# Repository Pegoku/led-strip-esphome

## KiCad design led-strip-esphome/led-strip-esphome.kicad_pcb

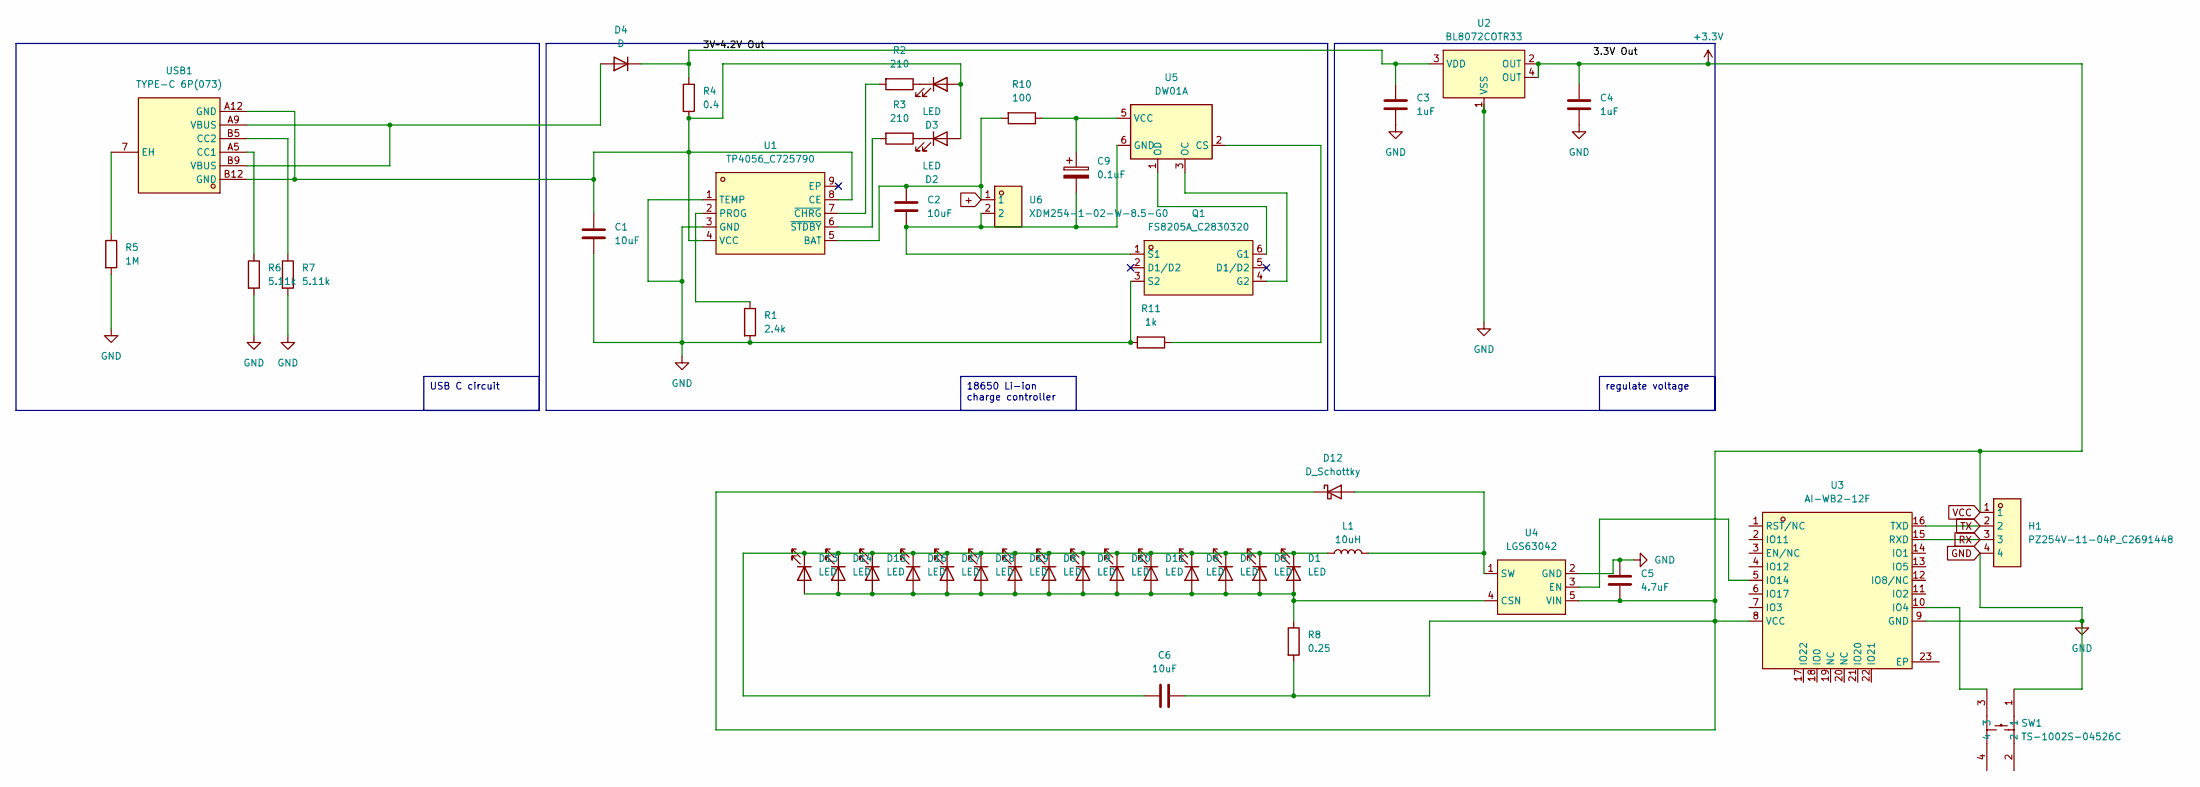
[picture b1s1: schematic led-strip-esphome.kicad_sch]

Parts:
C1, C2, C6: 10uF; C_0805_2012Metric
C3, C4: 1uF; C_0805_2012Metric
C5: 4.7uF; C_0805_2012Metric
C9: 0.1uF; CP_Elec_4x5.4
D1, D5, D6, D7, D8, D9, D10, D11, D13, D14, D15, D16, D17, D18, D19: LED; LED_PLCC_2835; LCSC C7423443
D2: LED; LED_0603_1608Metric; LCSC C22371297
D3: LED; LED_0603_1608Metric; LCSC C84263
D4: D; D_SMA; LCSC C5154212
D12: D_Schottky; D_SMA; LCSC C5350986
H1: PZ254V-11-04P_C2691448; HDR-TH_4P-P2.54-V-M; LCSC Part C2691448
L1: 10uH; L_Ferrocore_DLG-0403; LCSC C2929419
Q1: FS8205A_C2830320; SOT-23-6_L2.9-W1.6-P0.95-LS2.8-BR; LCSC Part C2830320
R1: 2.4k; LED_0805_2012Metric
R2, R3: 210; LED_0805_2012Metric
R4: 0.4; LED_0805_2012Metric
R5: 1M; LED_0805_2012Metric
R6, R7: 5.11k; LED_0805_2012Metric
R8: 0.25; LED_0805_2012Metric
R10: 100; LED_0805_2012Metric
R11: 1k; LED_0805_2012Metric
SW1: TS-1002S-04526C; SW-SMD_4P-L6.0-W6.0-P4.50-LS9.0-2; LCSC Part C455109
U1: TP4056_C725790; ESOP-8_L4.9-W3.9-P1.27-LS6.0-BL-EP; LCSC Part C725790
U2: BL8072COTR33; TO-252-3_L6.6-W6.1-P2.28-LS10.1-BL; LCSC Part C5155191
U3: AI-WB2-12F; COMM-SMD_22P-L24.0-W16.0-P2.00_ZIGBEE; LCSC Part C5187541
U4: LGS63042; SOT-23-5_L2.9-W1.6-P0.95-LS2.8-BL; LCSC Part C5123978
U5: DW01A; SOT-23-6
U6: XDM254-1-02-W-8.5-G0; HDR-TH_2P-P2.54-H-F-W10.0-N; LCSC Part C19268733
USB1: TYPE-C 6P(073); TYPE-C-SMD_TYPE-C-6P_5; LCSC Part C668623

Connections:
+: C2.2, R10.2, U1.5 (BAT), U6.1
/3V~4.2V Out: C3.1, D4.1 (K), R4.1, U2.3 (VDD)
GND: C1.1, C3.2, C4.2, C5.1, H1.4, Q1.3 (S2), R1.2, R5.2, R6.2, R7.2, R11.2, SW1.1, U1.1 (TEMP), U1.3 (GND), U2.1 (VSS), U3.9 (GND), U4.2 (GND)
unnamed: D1.2 (A), D5.2 (A), D6.2 (A), D7.2 (A), D8.2 (A), D9.2 (A), D10.2 (A), D11.2 (A), D13.2 (A), D14.2 (A), D15.2 (A), D16.2 (A), D17.2 (A), D18.2 (A), D19.2 (A), R8.1, U4.4 (CSN)
unnamed: C6.1, D1.1 (K), D5.1 (K), D6.1 (K), D7.1 (K), D8.1 (K), D9.1 (K), D10.1 (K), D11.1 (K), D13.1 (K), D14.1 (K), D15.1 (K), D16.1 (K), D17.1 (K), D18.1 (K), D19.1 (K), L1.1
unnamed: C1.2, D2.2 (A), D3.2 (A), R4.2, U1.4 (VCC), U1.8 (CE), USB1.A12 (GND), USB1.B12 (GND)
unnamed: D2.1 (K), R3.1
unnamed: D3.1 (K), R2.1
unnamed: D4.2 (A), USB1.A9 (VBUS), USB1.B9 (VBUS)
unnamed: D12.2 (A), L1.2, U4.1 (SW)
unnamed: Q1.6 (G1), U5.1 (OD)
unnamed: Q1.4 (G2), U5.3 (OC)
unnamed: C2.1, C9.2, Q1.1 (S1), U5.6 (GND), U6.2
unnamed: R1.1, U1.2 (PROG)
unnamed: R2.2, U1.7 (~CHRG)
unnamed: R3.2, U1.6 (~STDBY)
unnamed: SW1.3, U3.10 (IO4)
unnamed: U3.5 (IO14), U4.3 (EN)
unnamed: R11.1, U5.2 (CS)
unnamed: C9.1, R10.1, U5.5 (VCC)
unnamed: R6.1, USB1.A5 (CC1)
unnamed: R7.1, USB1.B5 (CC2)
unnamed: R5.1, USB1.7 (EH)
RX: H1.3, U3.15 (RXD)
TX: H1.2, U3.16 (TXD)
VCC: C4.1, C5.2, C6.2, D12.1 (K), H1.1, R8.2, U2.2 (OUT), U2.4 (OUT), U3.8 (VCC), U4.5 (VIN)

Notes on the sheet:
18650 Li-ion charge controller
regulate voltage
USB C circuit

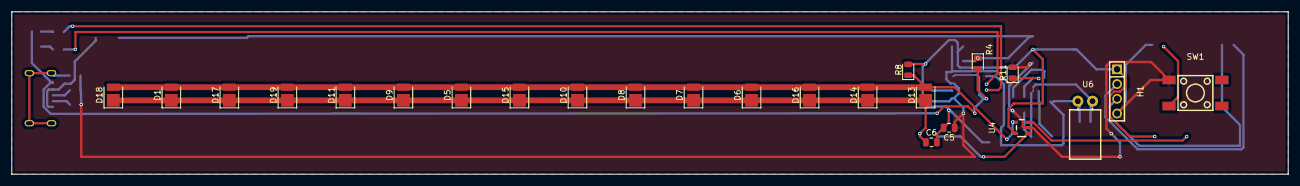
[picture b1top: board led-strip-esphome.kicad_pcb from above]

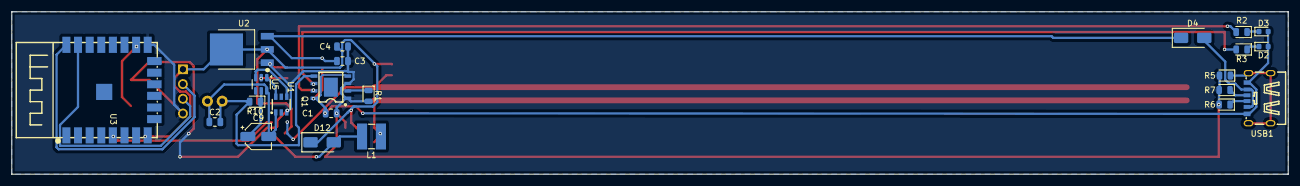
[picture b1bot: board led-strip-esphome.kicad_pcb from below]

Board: 2 copper layers, 220.0 x 28.0 mm, 47 parts (23 on the bottom side), 26 nets.

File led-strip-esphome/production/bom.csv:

Designator,Footprint,Quantity,Value,LCSC Part #
"C1, C2, C6",0805,3,10uF,
"C3, C4",0805,2,1uF,
C5,0805,1,4.7uF,
C9,CP_Elec_4x5.4,1,0.1uF,
"D1, D10, D11, D13, D14, D15, D16, D17, D18, D19, D5, D6, D7, D8, D9",LED_PLCC_2835,15,LED,C7423443
D12,D_SMA,1,D_Schottky,C5350986
D2,0603,1,LED,C22371297
D3,0603,1,LED,C84263
D4,D_SMA,1,D,C5154212
H1,HDR-TH_4P-P2.54-V-M,1,PZ254V-11-04P_C2691448,C2691448
L1,L_Ferrocore_DLG-0403,1,10uH,C2929419
Q1,SOT-23-6_L2.9-W1.6-P0.95-LS2.8-BR,1,FS8205A_C2830320,C2830320
R1,0805,1,2.4k,
R10,0805,1,100,
R11,0805,1,1k,
"R2, R3",0805,2,210,
R4,0805,1,0.4,
R5,0805,1,1M,
"R6, R7",0805,2,5.11k,
R8,0805,1,0.25,
SW1,SW-SMD_4P-L6.0-W6.0-P4.50-LS9.0-2,1,TS-1002S-04526C,C455109
U1,ESOP-8_L4.9-W3.9-P1.27-LS6.0-BL-EP,1,TP4056_C725790,C725790
U2,TO-252-3_L6.6-W6.1-P2.28-LS10.1-BL,1,BL8072COTR33,C5155191
U3,COMM-SMD_22P-L24.0-W16.0-P2.00_ZIGBEE,1,AI-WB2-12F,C5187541
U4,SOT-23-5_L2.9-W1.6-P0.95-LS2.8-BL,1,LGS63042,C5123978
U5,SOT-23-6,1,DW01A,
U6,HDR-TH_2P-P2.54-H-F-W10.0-N,1,XDM254-1-02-W-8.5-G0,C19268733
USB1,TYPE-C-SMD_TYPE-C-6P_5,1,TYPE-C 6P(073),C668623

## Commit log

2024-08-08 start
2024-08-08 schematic finished
2024-08-08 add footprints
2024-08-08 finished routing
2024-08-08 routing
2024-08-08 finishing
2024-08-08 finished
